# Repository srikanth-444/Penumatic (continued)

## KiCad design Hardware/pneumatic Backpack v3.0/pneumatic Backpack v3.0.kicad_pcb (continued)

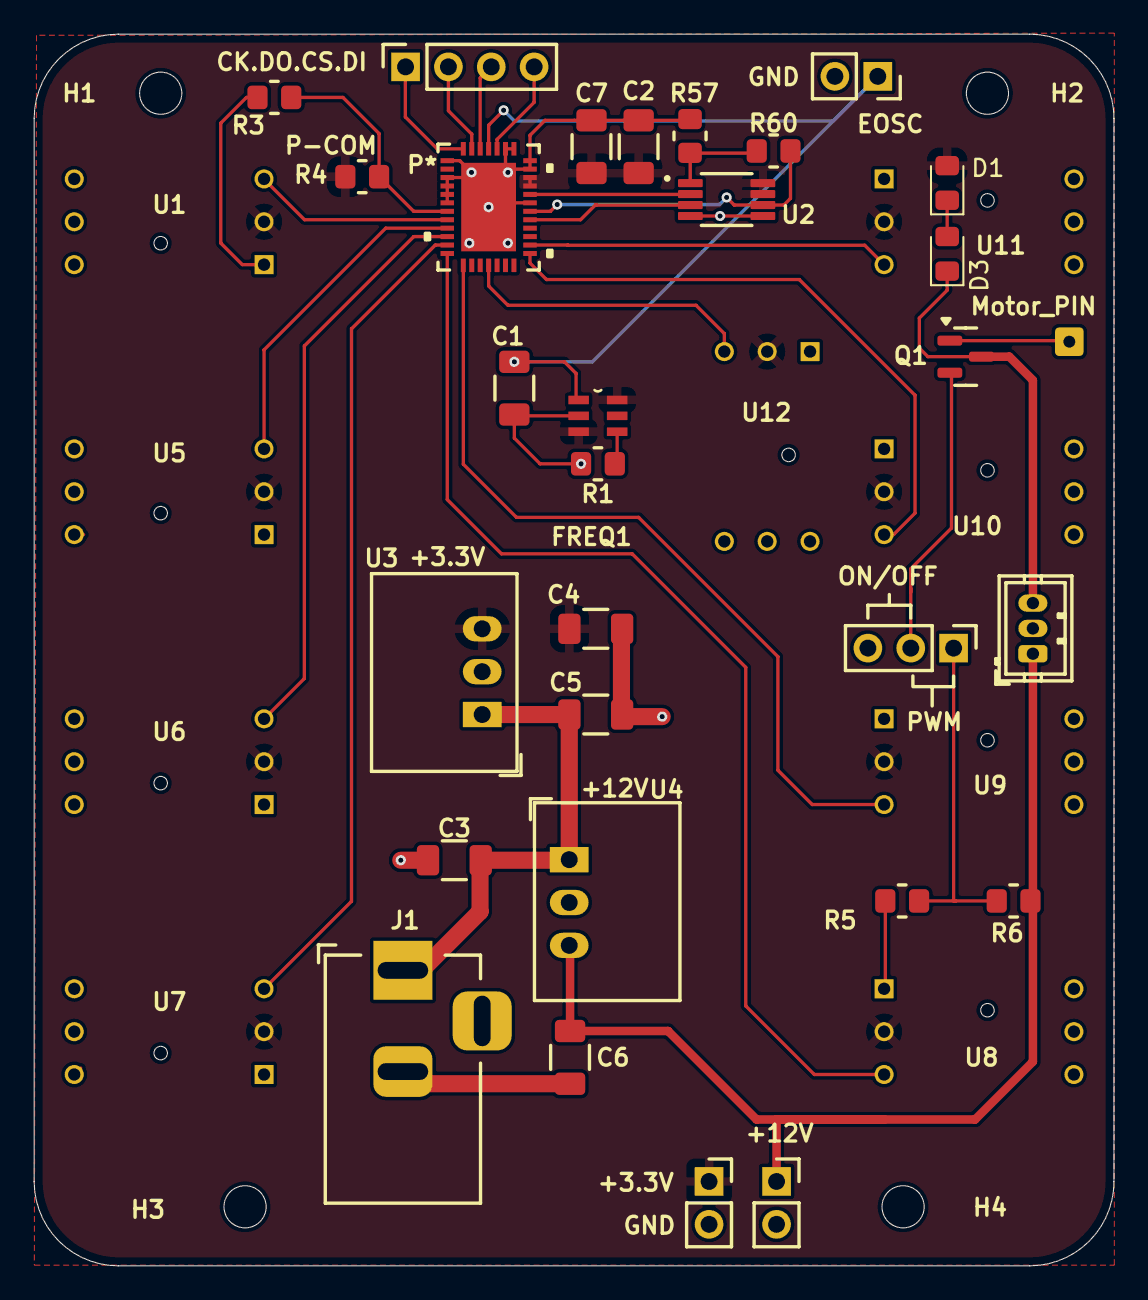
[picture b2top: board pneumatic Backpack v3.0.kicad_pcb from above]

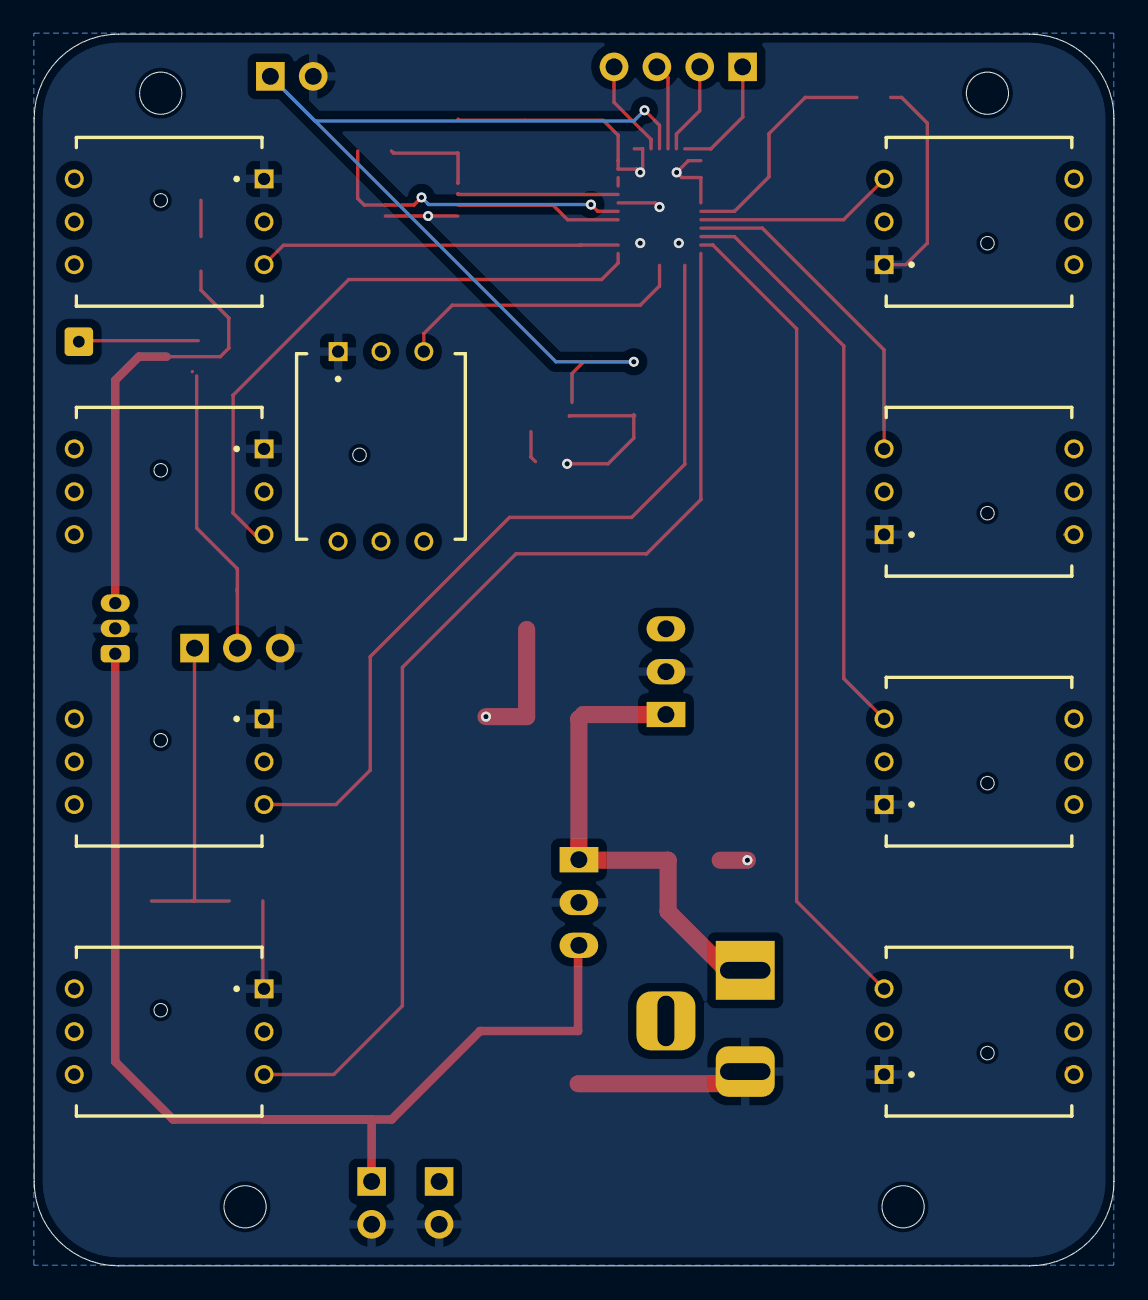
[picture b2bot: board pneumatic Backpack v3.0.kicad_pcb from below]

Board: 2 copper layers, 64.0 x 73.0 mm, 43 parts (9 on the bottom side), 29 nets.

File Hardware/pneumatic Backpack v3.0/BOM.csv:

"Reference","Value","Datasheet","Footprint","Qty","DNP"
"A1","LTC2498IUHF_TRPBF","","mod:QFN-38_UHF","1",""
"Bus_D1","Conn_01x04_Pin","~","Connector_PinSocket_2.54mm:PinSocket_1x04_P2.54mm_Vertical","1",""
"C1","5pf","~","Capacitor_SMD:C_1206_3216Metric_Pad1.33x1.80mm_HandSolder","1",""
"C2","0.1uf","~","Capacitor_SMD:C_1206_3216Metric_Pad1.33x1.80mm_HandSolder","1",""
"C3,C4,C5,C6","4.7uf","~","Capacitor_SMD:C_1206_3216Metric_Pad1.33x1.80mm_HandSolder","4",""
"C7","10uf","~","Capacitor_SMD:C_1206_3216Metric_Pad1.33x1.80mm_HandSolder","1",""
"D1","LED","~","LED_SMD:LED_0805_2012Metric_Pad1.15x1.40mm_HandSolder","1",""
"D3","D","~","Diode_SMD:D_0805_2012Metric_Pad1.15x1.40mm_HandSolder","1",""
"FREQ1","LTC6906IS6_TRPBF","","mod:SOT95P280X100-6N","1",""
"J1","Barrel_Jack_MountingPin","~","Connector_BarrelJack:BarrelJack_Horizontal","1",""
"J2,J9,J11","Conn_01x02_Pin","~","Connector_PinSocket_2.54mm:PinSocket_1x02_P2.54mm_Vertical","3",""
"J3,J4","Conn_01x03_Pin","~","-- mixed values --","2",""
"J5","Conn_01x01_Pin","~","Connector_Wire:SolderWire-0.15sqmm_1x01_D0.5mm_OD1.5mm","1",""
"Q1","AO3400A","http://www.aosmd.com/pdfs/datasheet/AO3400A.pdf","Package_TO_SOT_SMD:SOT-23","1",""
"R1,R3,R4,R57,R60","100k","~","Resistor_SMD:R_0805_2012Metric_Pad1.20x1.40mm_HandSolder","5",""
"R5","70","~","Resistor_SMD:R_0805_2012Metric_Pad1.20x1.40mm_HandSolder","1",""
"R6","50","~","Resistor_SMD:R_0805_2012Metric_Pad1.20x1.40mm_HandSolder","1",""
"U1,U5,U6,U7,U8,U9,U10,U11,U12","ABPDLNN100MG2A3","","ABPDLNN100MG2A3:XDCR_ABPDLNN100MG2A3","9",""
"U2","INA332AIDGKR","","INA332AIDGKR:SOP65P490X110-8N","1",""
"U3","R-78C3.3-1.0","https://www.recom-power.com/pdf/Innoline/R-78Cxx-1.0.pdf","Converter_DCDC:Converter_DCDC_RECOM_R-78E-0.5_THT","1",""
"U4","R-78C12-1.0","https://www.recom-power.com/pdf/Innoline/R-78Cxx-1.0.pdf","Converter_DCDC:Converter_DCDC_RECOM_R-78E-0.5_THT","1",""

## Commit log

2025-09-18 initial push
2025-09-27 created Serif
2025-09-29 test run 1
2026-02-18 Initial clean commit - firmware + PCB source only
2026-02-18 bom fell
2026-03-12 cleaning code
2026-03-12 Rename project to 'Peumatic Backpack' and clean README
    Updated project name and removed outdated example content.
2026-03-12 clean
2026-03-12 Add interactive schematic badge to README
    Added a badge linking to the interactive schematic.
2026-03-12 Fix capitalization in PCB image rendering step
2026-03-12 Update README with project details and images
    Added project description and image placeholders.
2026-03-12 Update PCB file path in workflow configuration
2026-03-12 Update PCB file path for rendering
2026-03-12 Add images section to README
2026-03-12 Refactor PCB image rendering workflow
    Updated workflow to improve PCB image rendering and commit process.
2026-03-12 Modify PCB render workflow to skip CI on commit
    Updated commit message to skip CI for auto-updates.
2026-03-12 Auto-update PCB renders [skip ci]
2026-03-12 Update README to streamline image section
    Removed PCB description and combined image links.
2026-03-12 Change image display to centered HTML format
    Updated image display format in README.md for better alignment.
2026-03-12 Change image widths to 500px in README
    Updated image widths in the README file.
2026-03-12 Adjust image widths in README
    Updated image widths in README.md from 600 to 550.
2026-03-12 Adjust image widths in README
    Updated image widths in README.md from 550 to 500 pixels.
2026-03-12 Update PCB image rendering for top and bottom boards
2026-03-12 Update PCB file path for rendering workflow
2026-03-12 Refactor image paths in README.md
    Updated image paths in README for better organization.
2026-03-12 Update PCB image workflow to include new board version
2026-03-12 Add JLCPCB configuration for gerbers and drill files
2026-03-12 Update config path for Gerber output in workflow
2026-03-12 Set KiCad version to 8 in pcb-image.yml
    Updated KiCad board version to 8 for both v3.0 and v3.1.
2026-03-12 added diods to the leds
2026-03-12 Add path filter for Hardware directory in workflow
